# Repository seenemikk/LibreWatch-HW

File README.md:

# LibreWatch-HW

This repository contains hardware related files for [LibreWatch](https://github.com/seenemikk/LibreWatch) smartwatch.

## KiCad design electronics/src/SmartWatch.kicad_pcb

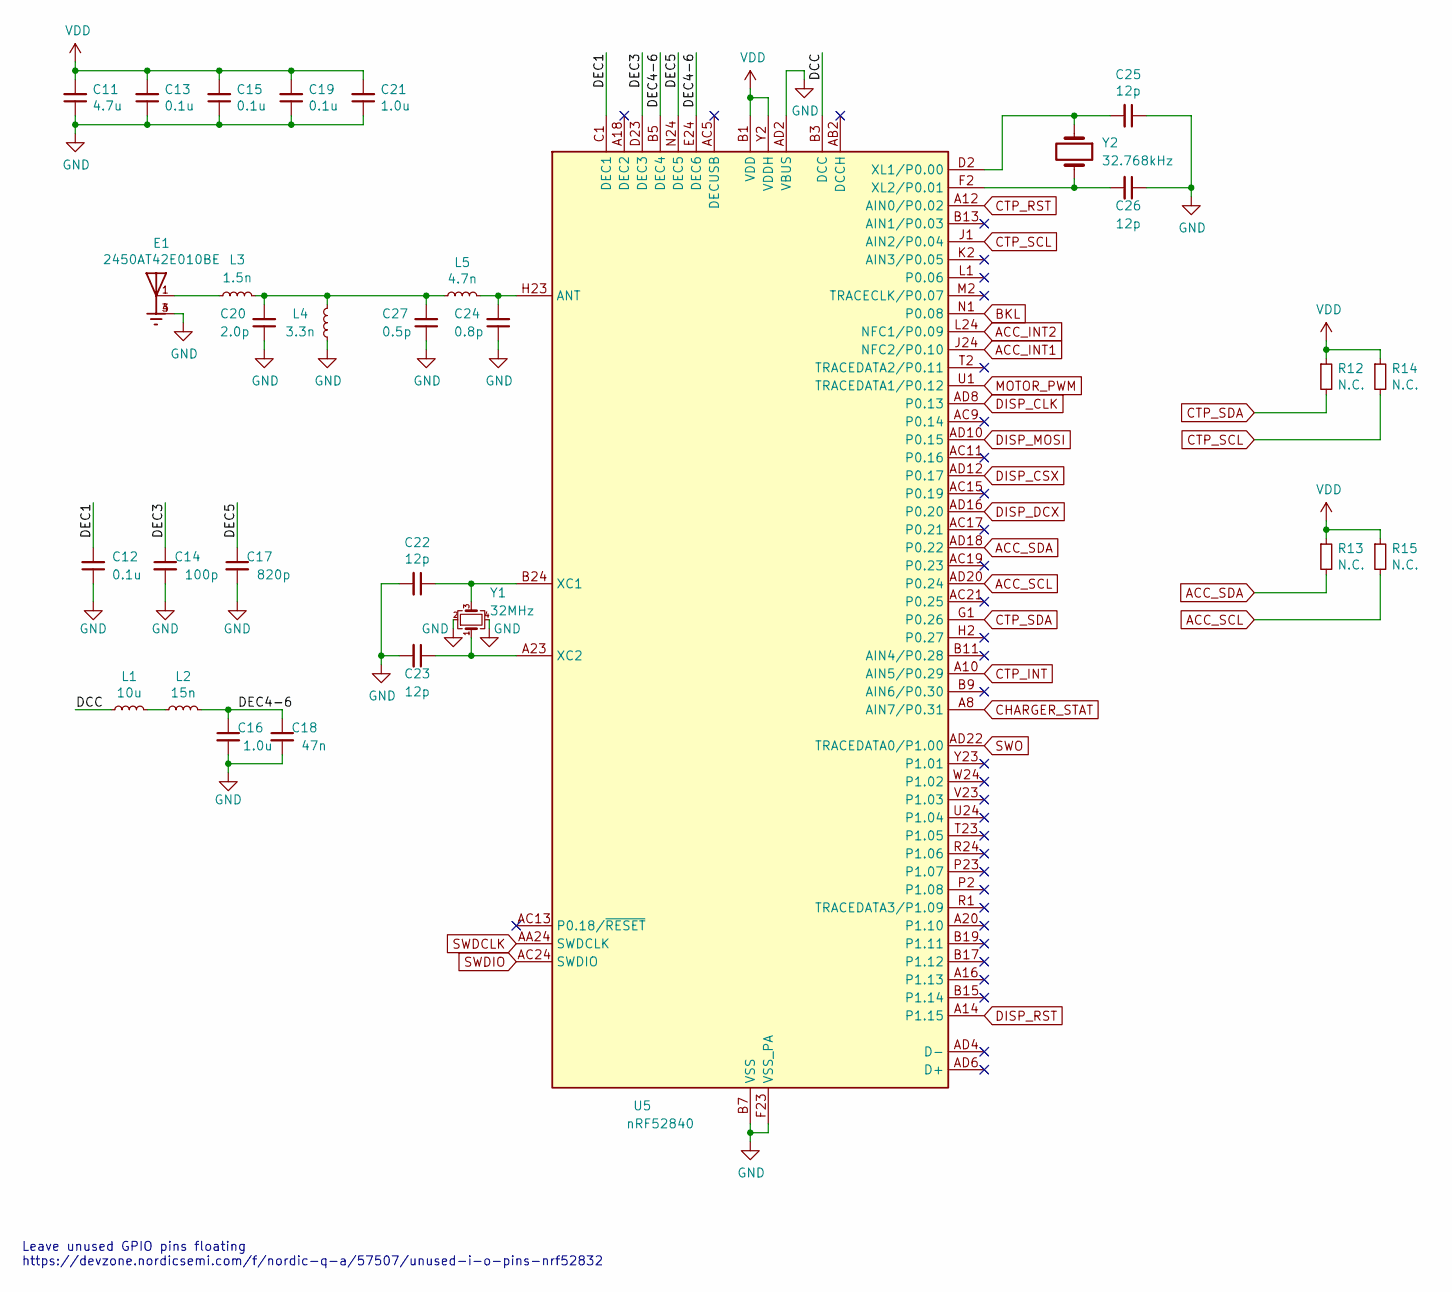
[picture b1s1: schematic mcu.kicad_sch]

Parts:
C11: 4.7u; C_0603_1608Metric
C12, C13, C15, C19: 0.1u; C_0402_1005Metric
C14: 100p; C_0402_1005Metric
C16, C21: 1.0u; C_0603_1608Metric
C17: 820p; C_0402_1005Metric
C18: 47n; C_0402_1005Metric
C20: 2.0p; C_0402_1005Metric
C22, C23, C25, C26: 12p; C_0402_1005Metric
C24: 0.8p; C_0402_1005Metric
C27: 0.5p; C_0402_1005Metric
E1: 2450AT42E010BE; XDCR_2450AT42E010BE; PARTREV 1.3
L1: 10u; L_0603_1608Metric
L2: 15n; L_0402_1005Metric
L3: 1.5n; L_0402_1005Metric
L4: 3.3n; L_0402_1005Metric
L5: 4.7n; L_0402_1005Metric
R12, R13, R14, R15: N.C.; R_0402_1005Metric
U5: nRF52840; Nordic_AQFN-73-1EP_7x7mm_P0.5mm
Y1: 32MHz; Crystal_SMD_2016-4Pin_2.0x1.6mm
Y2: 32.768kHz; Crystal_SMD_2012-2Pin_2.0x1.2mm

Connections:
/MCU/DCC: L1.1, U5.B3 (DCC)
/MCU/DEC1: C12.2, U5.C1 (DEC1)
/MCU/DEC3: C14.1, U5.D23 (DEC3)
/MCU/DEC4-6: C16.1, C18.1, L2.2, U5.B5 (DEC4), U5.E24 (DEC6)
/MCU/DEC5: C17.1, U5.N24 (DEC5)
ACC_INT1: U5.J24 (NFC2/P0.10); also elsewhere on the board
ACC_INT2: U5.L24 (NFC1/P0.09); also elsewhere on the board
ACC_SCL: R15.2, U5.AD20 (P0.24); also elsewhere on the board
ACC_SDA: R13.2, U5.AD18 (P0.22); also elsewhere on the board
BKL: U5.N1 (P0.08); also elsewhere on the board
CHARGER_STAT: U5.A8 (AIN7/P0.31); also elsewhere on the board
CTP_INT: U5.A10 (AIN5/P0.29); also elsewhere on the board
CTP_RST: U5.A12 (AIN0/P0.02); also elsewhere on the board
CTP_SCL: R14.2, U5.J1 (AIN2/P0.04); also elsewhere on the board
CTP_SDA: R12.2, U5.G1 (P0.26); also elsewhere on the board
DISP_CLK: U5.AD8 (P0.13); also elsewhere on the board
DISP_CSX: U5.AD12 (P0.17); also elsewhere on the board
DISP_DCX: U5.AD16 (P0.20); also elsewhere on the board
DISP_MOSI: U5.AD10 (P0.15); also elsewhere on the board
DISP_RST: U5.A14 (P1.15); also elsewhere on the board
GND: C11.1, C12.1, C13.1, C14.2, C15.1, C16.2, C17.2, C18.2, C19.1, C20.1, C21.1, C22.2, C23.2, C24.1, C25.1, C26.1, C27.1, E1.3, E1.4, L4.1, U5.AD2 (VBUS), U5.B7 (VSS), U5.EP (VSS), U5.F23 (VSS_PA), Y1.2, Y1.4; also elsewhere on the board
MOTOR_PWM: U5.U1 (TRACEDATA1/P0.12); also elsewhere on the board
unnamed: C20.2, C27.2, L3.2, L4.2, L5.1
unnamed: C22.1, U5.B24 (XC1), Y1.3
unnamed: C23.1, U5.A23 (XC2), Y1.1
unnamed: C24.2, L5.2, U5.H23 (ANT)
unnamed: C25.2, U5.D2 (XL1/P0.00), Y2.1
unnamed: C26.2, U5.F2 (XL2/P0.01), Y2.2
unnamed: E1.1, L3.1
unnamed: L1.2, L2.1
SWDCLK: U5.AA24 (SWDCLK); also elsewhere on the board
SWDIO: U5.AC24 (SWDIO); also elsewhere on the board
SWO: U5.AD22 (TRACEDATA0/P1.00); also elsewhere on the board
VDD: C11.2, C13.2, C15.2, C19.2, C21.2, R12.1, R13.1, R14.1, R15.1, U5.A22 (VDD), U5.AD14 (VDD), U5.AD23 (VDD), U5.B1 (VDD), U5.W1 (VDD), U5.Y2 (VDDH); also elsewhere on the board

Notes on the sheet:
Leave unused GPIO pins floating https://devzone.nordicsemi.com/f/nordic-q-a/57507/unused-i-o-pins-nrf52832

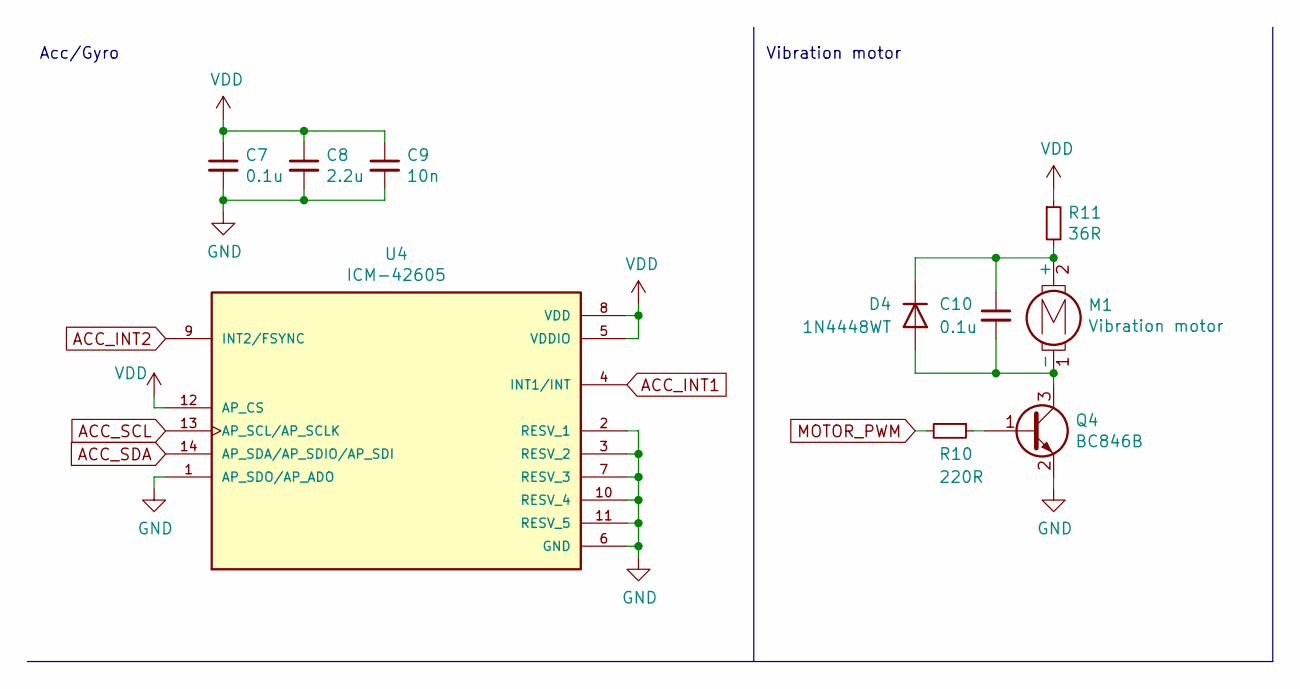
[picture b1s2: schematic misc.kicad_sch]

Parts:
C7: 0.1u; C_0402_1005Metric
C8: 2.2u; C_0402_1005Metric
C9: 10n; C_0402_1005Metric
C10: 0.1u; C_0603_1608Metric
D4: 1N4448WT; SOD-523F
M1: Vibration motor; Battery_Pads
Q4: BC846B; SOT-23
R10: 220R; R_0402_1005Metric
R11: 36R; R_0603_1608Metric
U4: ICM-42605; PQFN50P300X250X97-14N; PARTREV 0.4

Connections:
ACC_INT1: U4.4 (INT1/INT); also elsewhere on the board
ACC_INT2: U4.9 (INT2/FSYNC); also elsewhere on the board
ACC_SCL: U4.13 (AP_SCL/AP_SCLK); also elsewhere on the board
ACC_SDA: U4.14 (AP_SDA/AP_SDIO/AP_SDI); also elsewhere on the board
GND: C7.2, C8.2, C9.2, Q4.2 (E), U4.1 (AP_SDO/AP_ADO), U4.2 (RESV_1), U4.3 (RESV_2), U4.6 (GND), U4.7 (RESV_3), U4.10 (RESV_4), U4.11 (RESV_5); also elsewhere on the board
MOTOR_PWM: R10.2; also elsewhere on the board
unnamed: C10.1, D4.1 (K), M1.2 (+), R11.2
unnamed: C10.2, D4.2 (A), M1.1 (-), Q4.3 (C)
unnamed: Q4.1 (B), R10.1
VDD: C7.1, C8.1, C9.1, R11.1, U4.5 (VDDIO), U4.8 (VDD), U4.12 (AP_CS); also elsewhere on the board

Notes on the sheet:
Acc/Gyro
Vibration motor

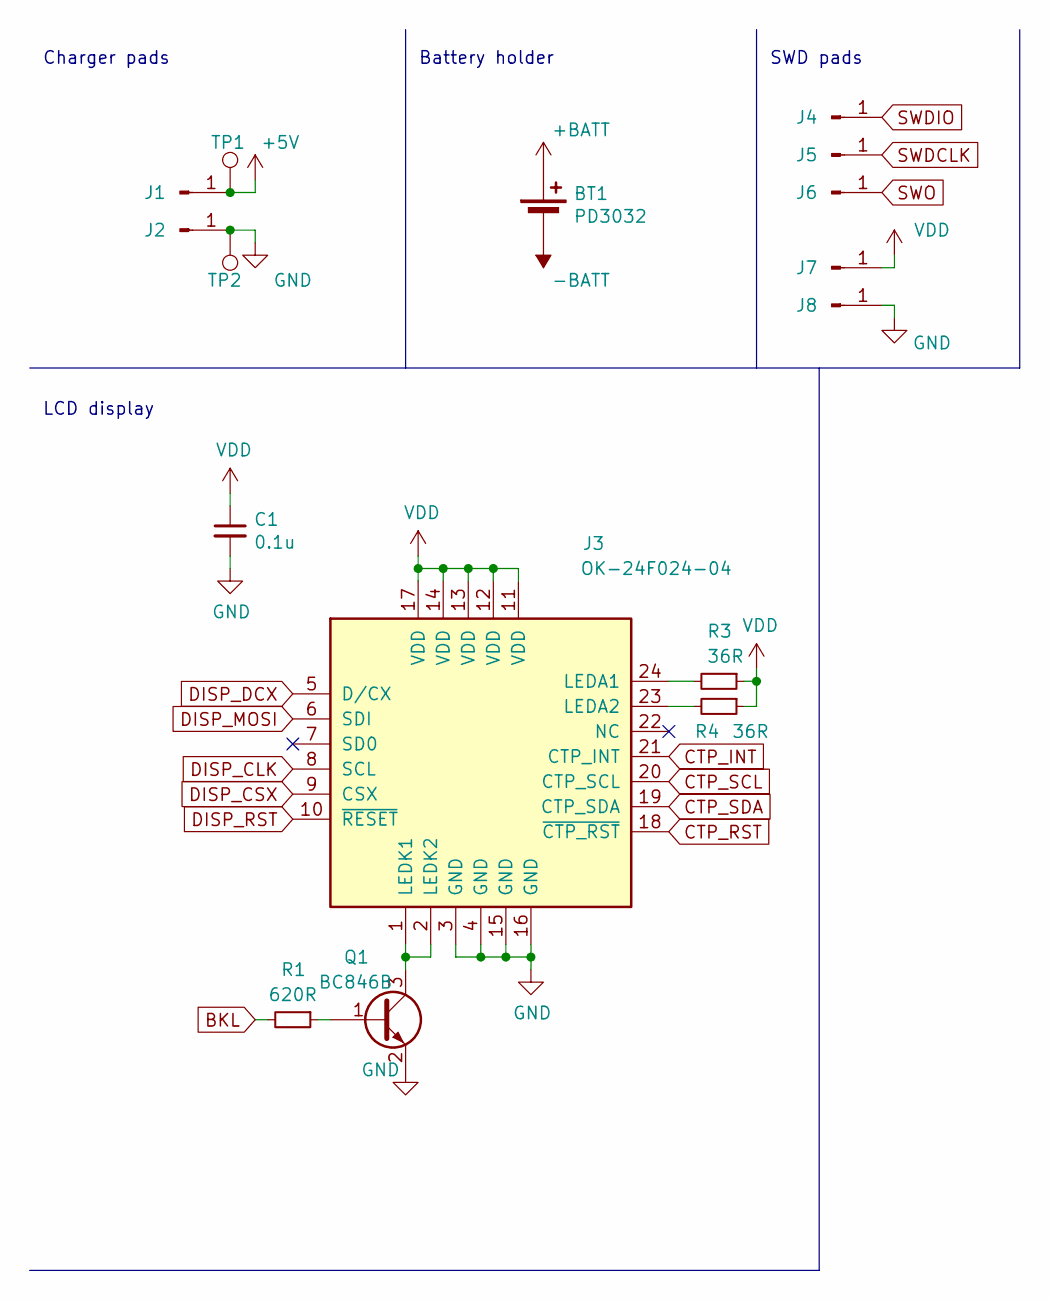
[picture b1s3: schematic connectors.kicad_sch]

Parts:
BT1: PD3032; Battery_Pads
C1: 0.1u; C_0402_1005Metric
J1, J2: P70-2010045R; TestPoint_Pad_D1.5mm
J3: OK-24F024-04
J4, J5, J6, J7, J8: P70-2010045R; TestPoint_Pad_D2.5mm
Q1: BC846B; SOT-23
R1: 620R; R_0402_1005Metric
R3, R4: 36R; R_0402_1005Metric
TP1, TP2: TestPoint; TestPoint_Pad_D1.5mm

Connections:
+5V: J1.1, TP1.1; also elsewhere on the board
+BATT: BT1.1 (+); also elsewhere on the board
-BATT: BT1.2 (-); also elsewhere on the board
BKL: R1.2; also elsewhere on the board
CTP_INT: J3.21 (CTP_INT); also elsewhere on the board
CTP_RST: J3.18 (~CTP_RST); also elsewhere on the board
CTP_SCL: J3.20 (CTP_SCL); also elsewhere on the board
CTP_SDA: J3.19 (CTP_SDA); also elsewhere on the board
DISP_CLK: J3.8 (SCL); also elsewhere on the board
DISP_CSX: J3.9 (CSX); also elsewhere on the board
DISP_DCX: J3.5 (D/CX); also elsewhere on the board
DISP_MOSI: J3.6 (SDI); also elsewhere on the board
DISP_RST: J3.10 (~RESET); also elsewhere on the board
GND: C1.2, J2.1, J3.3 (GND), J3.4 (GND), J3.15 (GND), J3.16 (GND), J8.1, Q1.2 (E), TP2.1; also elsewhere on the board
unnamed: J3.1 (LEDK1), J3.2 (LEDK2), Q1.3 (C)
unnamed: J3.23 (LEDA2), R4.2
unnamed: J3.24 (LEDA1), R3.2
unnamed: Q1.1 (B), R1.1
SWDCLK: J5.1; also elsewhere on the board
SWDIO: J4.1; also elsewhere on the board
SWO: J6.1; also elsewhere on the board
VDD: C1.1, J3.11 (VDD), J3.12 (VDD), J3.13 (VDD), J3.14 (VDD), J3.17 (VDD), J7.1, R3.1, R4.1; also elsewhere on the board

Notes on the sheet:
SWD pads
Battery holder
LCD display
Charger pads

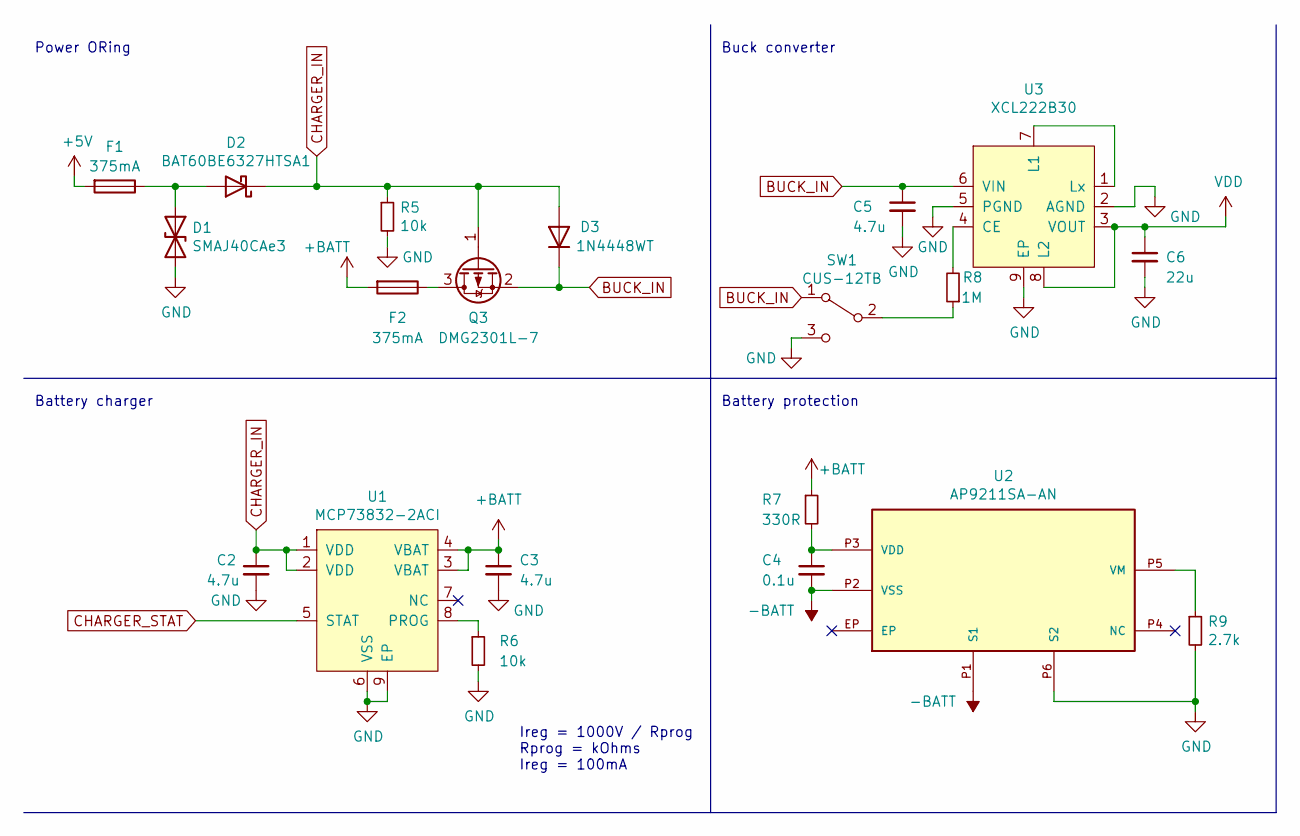
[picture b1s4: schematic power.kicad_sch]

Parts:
C2, C3, C5: 4.7u; C_0603_1608Metric
C4: 0.1u; C_0603_1608Metric
C6: 22u; C_0603_1608Metric
D1: SMAJ40CAe3; D_SMA
D2: BAT60BE6327HTSA1; D_SOD-323
D3: 1N4448WT; SOD-523F
F1, F2: 375mA; Fuse_0603_1608Metric
Q3: DMG2301L-7; SOT-23
R5, R6: 10k; R_0402_1005Metric
R7: 330R; R_0603_1608Metric
R8: 1M; R_0402_1005Metric
R9: 2.7k; R_0603_1608Metric
SW1: CUS-12TB; CUS-12B
U1: MCP73832-2ACI
U2: AP9211SA-AN; U-DFN2030-6
U3: XCL222B30; VREG_XCL220B283FR-G

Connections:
+5V: F1.2; also elsewhere on the board
+BATT: C3.1, F2.2, R7.1, U1.3 (VBAT), U1.4 (VBAT); also elsewhere on the board
-BATT: C4.2, U2.P1 (S1), U2.P2 (VSS); also elsewhere on the board
BUCK_IN: C5.1, D3.1 (K), Q3.2 (S), SW1.1 (A), U3.6 (VIN)
CHARGER_IN: C2.1, D2.1 (K), D3.2 (A), Q3.1 (G), R5.1, U1.1 (VDD), U1.2 (VDD)
CHARGER_STAT: U1.5 (STAT); also elsewhere on the board
GND: C2.2, C3.2, C5.2, C6.2, D1.2 (A2), R5.2, R6.2, R9.2, SW1.3 (C), U1.6 (VSS), U1.9 (EP), U2.P6 (S2), U3.2 (AGND), U3.5 (PGND), U3.9 (EP); also elsewhere on the board
unnamed: C4.1, R7.2, U2.P3 (VDD)
unnamed: D1.1 (A1), D2.2 (A), F1.1
unnamed: F2.1, Q3.3 (D)
unnamed: R6.1, U1.8 (PROG)
unnamed: R8.1, SW1.2 (B)
unnamed: R8.2, U3.4 (CE)
unnamed: R9.1, U2.P5 (VM)
unnamed: U3.1 (Lx), U3.7 (L1)
VDD: C6.1, U3.3 (VOUT), U3.8 (L2); also elsewhere on the board

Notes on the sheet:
Power ORing
Battery protection
Ireg = 1000V / Rprog Rprog = kOhms Ireg = 100mA
Buck converter
Battery charger

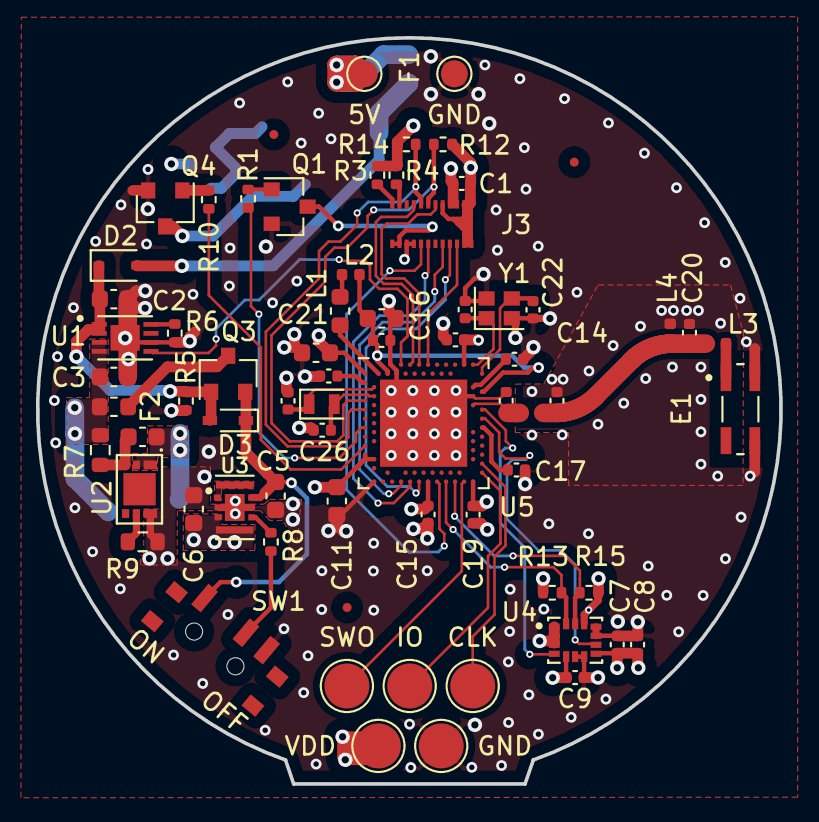
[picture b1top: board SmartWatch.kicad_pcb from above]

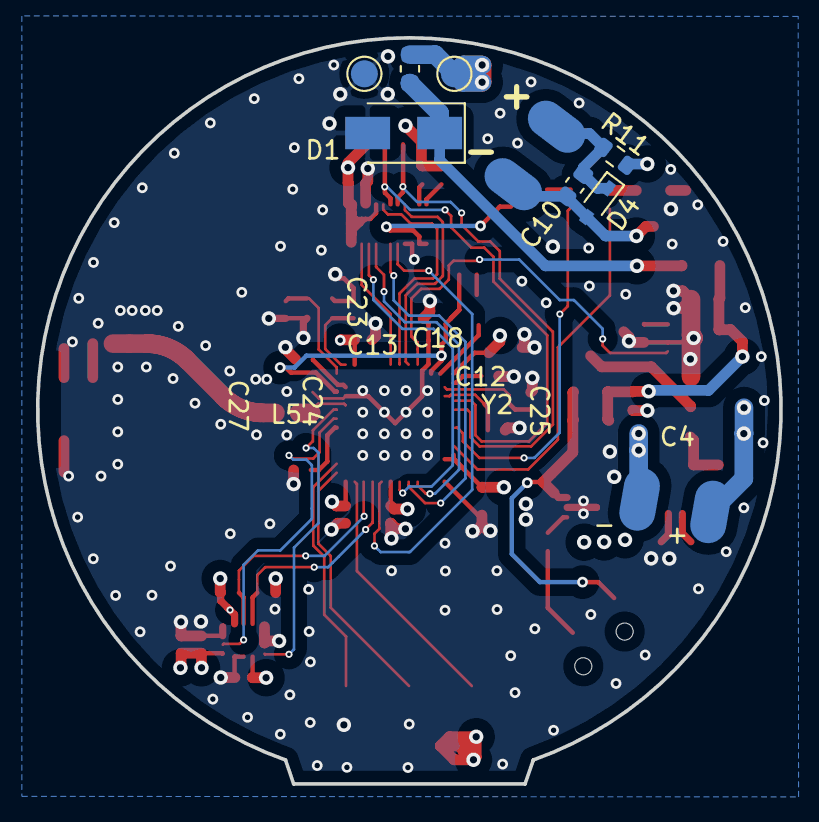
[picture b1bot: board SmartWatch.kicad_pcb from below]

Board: 4 copper layers, 41.3 x 41.5 mm, 76 parts (9 on the bottom side), 54 nets.

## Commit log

2023-06-04 Create LICENSE
